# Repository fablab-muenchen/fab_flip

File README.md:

# fab_flip
Flip dot/flip digit stuff

_

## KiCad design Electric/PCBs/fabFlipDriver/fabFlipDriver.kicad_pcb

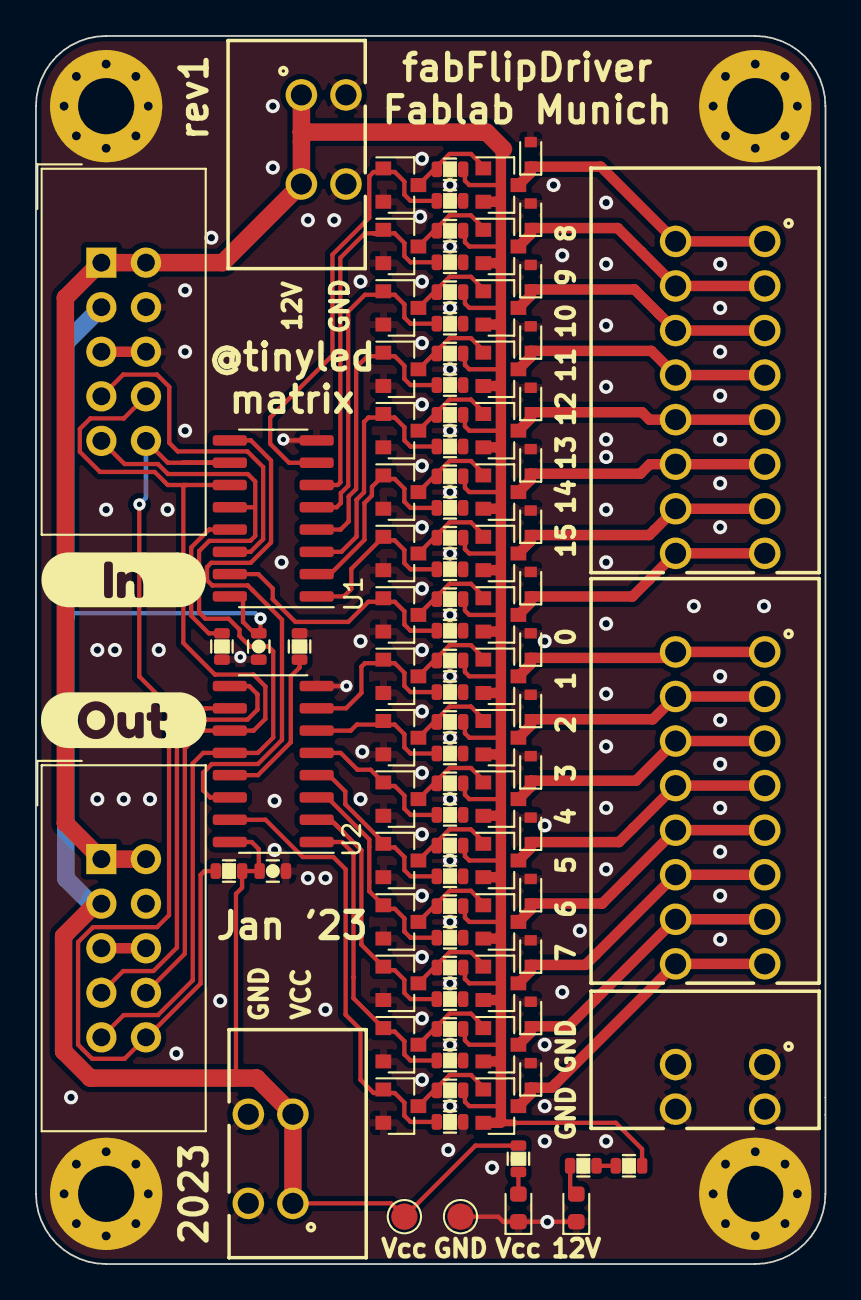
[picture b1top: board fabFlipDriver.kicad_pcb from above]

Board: 2 copper layers, 45.0 x 70.0 mm, 107 parts (0 on the bottom side), 62 nets.

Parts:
C1, C2: 100n; C_0603
D1, D2: LED; LED_0603_1608Metric
D3, D4, D5, D6, D7, D8, D9, D10, D11, D12, D13, D14, D15, D16, D17, D18: D; D_SOD-523
H1, H2, H3, H4: MountingHole_Pad; MountingHole_3.2mm_M3_Pad_Via
J1, J2: Conn_02x05_Odd_Even; IDC-Header_2x05_P2.54mm_Vertical
J3, J4: Conn_01x08; WE_691403900008B
J5, J6, J7: Conn_01x02; WE_691403900002B
Q1, Q2, Q5, Q6, Q9, Q10, Q13, Q14, Q17, Q18, Q21, Q22, Q25, Q26, Q29, Q30: AO3401A; SOT-23
Q3, Q4, Q7, Q8, Q11, Q12, Q15, Q16, Q19, Q20, Q23, Q24, Q27, Q28, Q31, Q32: 2N7002; SOT-23
R1, R2, R3, R4, R5, R6, R7, R8, R9, R10, R11, R12, R13, R14, R15, R16, R17, R18, R19, R20, R21, R22, R23, R24, R25, R26, R27, R28, R29, R30, R31, R32, R33, R34, R35: 10k; R_0603
R36, R37, R38: 1K; R_0603
TP2, TP3: TestPoint; TestPoint_Pad_D1.5mm
U1, U2: 74HC595; SOIC-16_3.9x9.9mm_P1.27mm
kibuzzard-63C33DE4: G***; kibuzzard-63C33DE4
kibuzzard-63C33DF7: G***; kibuzzard-63C33DF7

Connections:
+12V: J1.1, J1.2, J2.1, J2.2, J7.1, Q1.2 (S), Q2.2 (S), Q5.2 (S), Q6.2 (S), Q9.2 (S), Q10.2 (S), Q13.2 (S), Q14.2 (S), Q17.2 (S), Q18.2 (S), Q21.2 (S), Q22.2 (S), Q25.2 (S), Q26.2 (S), Q29.2 (S), Q30.2 (S), R2.1, R4.1, R6.1, R8.1, R11.1, R13.1, R15.1, R17.1, R20.1, R22.1, R25.1, R27.1, R29.1, R31.1, R33.1, R35.1, R36.1
/Bit00: Q4.1 (G), R3.2, U2.7 (QH)
/Bit01: Q8.1 (G), R7.2, U2.6 (QG)
/Bit02: Q12.1 (G), R12.2, U2.5 (QF)
/Bit03: Q16.1 (G), R16.2, U2.4 (QE)
/Bit04: Q20.1 (G), R21.2, U2.3 (QD)
/Bit05: Q24.1 (G), R26.2, U2.2 (QC)
/Bit06: Q28.1 (G), R30.2, U2.1 (QB)
/Bit07: Q32.1 (G), R34.2, U2.15 (QA)
/Bit08: Q3.1 (G), R1.2, U1.7 (QH)
/Bit09: Q7.1 (G), R5.2, U1.6 (QG)
/Bit10: Q11.1 (G), R10.2, U1.5 (QF)
/Bit11: Q15.1 (G), R14.2, U1.4 (QE)
/Bit12: Q19.1 (G), R19.2, U1.3 (QD)
/Bit13: Q23.1 (G), R24.2, U1.2 (QC)
/Bit14: Q27.1 (G), R28.2, U1.1 (QB)
/Bit15: Q31.1 (G), R32.2, U1.15 (QA)
/Clear: J1.10, J2.10, R18.1, U1.10 (~SRCLR), U2.10 (~SRCLR)
/Clock: J1.8, J2.8, U1.11 (SRCLK), U2.11 (SRCLK)
/Din: J1.7, U1.14 (SER)
/Dout: J2.7, U2.9 (QH')
/Latch: J1.9, J2.9, U1.12 (RCLK), U2.12 (RCLK)
/O_00: D4.1 (K), J4.1, Q2.3 (D)
/O_01: D6.1 (K), J4.2, Q6.3 (D)
/O_02: D8.1 (K), J4.3, Q10.3 (D)
/O_03: D10.1 (K), J4.4, Q14.3 (D)
/O_04: D12.1 (K), J4.5, Q18.3 (D)
/O_05: D14.1 (K), J4.6, Q22.3 (D)
/O_06: D16.1 (K), J4.7, Q26.3 (D)
/O_07: D18.1 (K), J4.8, Q30.3 (D)
/O_08: D3.1 (K), J3.1, Q1.3 (D)
/O_09: D5.1 (K), J3.2, Q5.3 (D)
/O_10: D7.1 (K), J3.3, Q9.3 (D)
/O_11: D9.1 (K), J3.4, Q13.3 (D)
/O_12: D11.1 (K), J3.5, Q17.3 (D)
/O_13: D13.1 (K), J3.6, Q21.3 (D)
/O_14: D15.1 (K), J3.7, Q25.3 (D)
/O_15: D17.1 (K), J3.8, Q29.3 (D)
GND: C1.1, C2.1, D1.1 (K), D2.1 (K), D3.2 (A), D4.2 (A), D5.2 (A), D6.2 (A), D7.2 (A), D8.2 (A), D9.2 (A), D10.2 (A), D11.2 (A), D12.2 (A), D13.2 (A), D14.2 (A), D15.2 (A), D16.2 (A), D17.2 (A), D18.2 (A), H1.1, H2.1, H3.1, H4.1, J1.4, J1.5, J1.6, J2.4, J2.5, J2.6, J5.1, J5.2, J6.2, J7.2, Q3.2 (S), Q4.2 (S), Q7.2 (S), Q8.2 (S), Q11.2 (S), Q12.2 (S), Q15.2 (S), Q16.2 (S), Q19.2 (S), Q20.2 (S), Q23.2 (S), Q24.2 (S), Q27.2 (S), Q28.2 (S), Q31.2 (S), Q32.2 (S), R1.1, R3.1, R5.1, R7.1, R9.2, R10.1, R12.1, R14.1, R16.1, R19.1, R21.1, R23.2, R24.1, R26.1, R28.1, R30.1, R32.1, R34.1, TP3.1, U1.8 (GND), U2.8 (GND)
unnamed: D1.2 (A), R37.2
unnamed: D2.2 (A), R38.2
unnamed: Q1.1 (G), Q3.3 (D), R2.2
unnamed: Q2.1 (G), Q4.3 (D), R4.2
unnamed: Q5.1 (G), Q7.3 (D), R6.2
unnamed: Q6.1 (G), Q8.3 (D), R8.2
unnamed: Q10.1 (G), Q12.3 (D), R13.2
unnamed: Q9.1 (G), Q11.3 (D), R11.2
unnamed: Q13.1 (G), Q15.3 (D), R15.2
unnamed: Q14.1 (G), Q16.3 (D), R17.2
unnamed: Q17.1 (G), Q19.3 (D), R20.2
unnamed: Q18.1 (G), Q20.3 (D), R22.2
unnamed: Q21.1 (G), Q23.3 (D), R25.2
unnamed: Q22.1 (G), Q24.3 (D), R27.2
unnamed: Q25.1 (G), Q27.3 (D), R29.2
unnamed: Q26.1 (G), Q28.3 (D), R31.2
unnamed: Q29.1 (G), Q31.3 (D), R33.2
unnamed: Q30.1 (G), Q32.3 (D), R35.2
unnamed: R9.1, U1.13 (~OE)
unnamed: R23.1, U2.13 (~OE)
unnamed: R36.2, R38.1
unnamed: U1.9 (QH'), U2.14 (SER)
VCC: C1.2, C2.2, J1.3, J2.3, J6.1, R18.2, R37.1, TP2.1, U1.16 (VCC), U2.16 (VCC)

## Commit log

2023-01-14 ersatzteil klappelem, 1st version
2023-01-14 Test if co
2023-01-15 First Push of PCB for Driver PCB
    Driver PCB is now in Git. Not Production ready yet
2023-01-15 Cleanup
2023-01-15 More cleanup
2023-01-15 Evan more cleanup
2023-01-15 PCB design finalized
    DRC okay
    should be ready for production
2023-01-15 minor change
2023-01-21 PCB update
2023-01-26 Small changes
